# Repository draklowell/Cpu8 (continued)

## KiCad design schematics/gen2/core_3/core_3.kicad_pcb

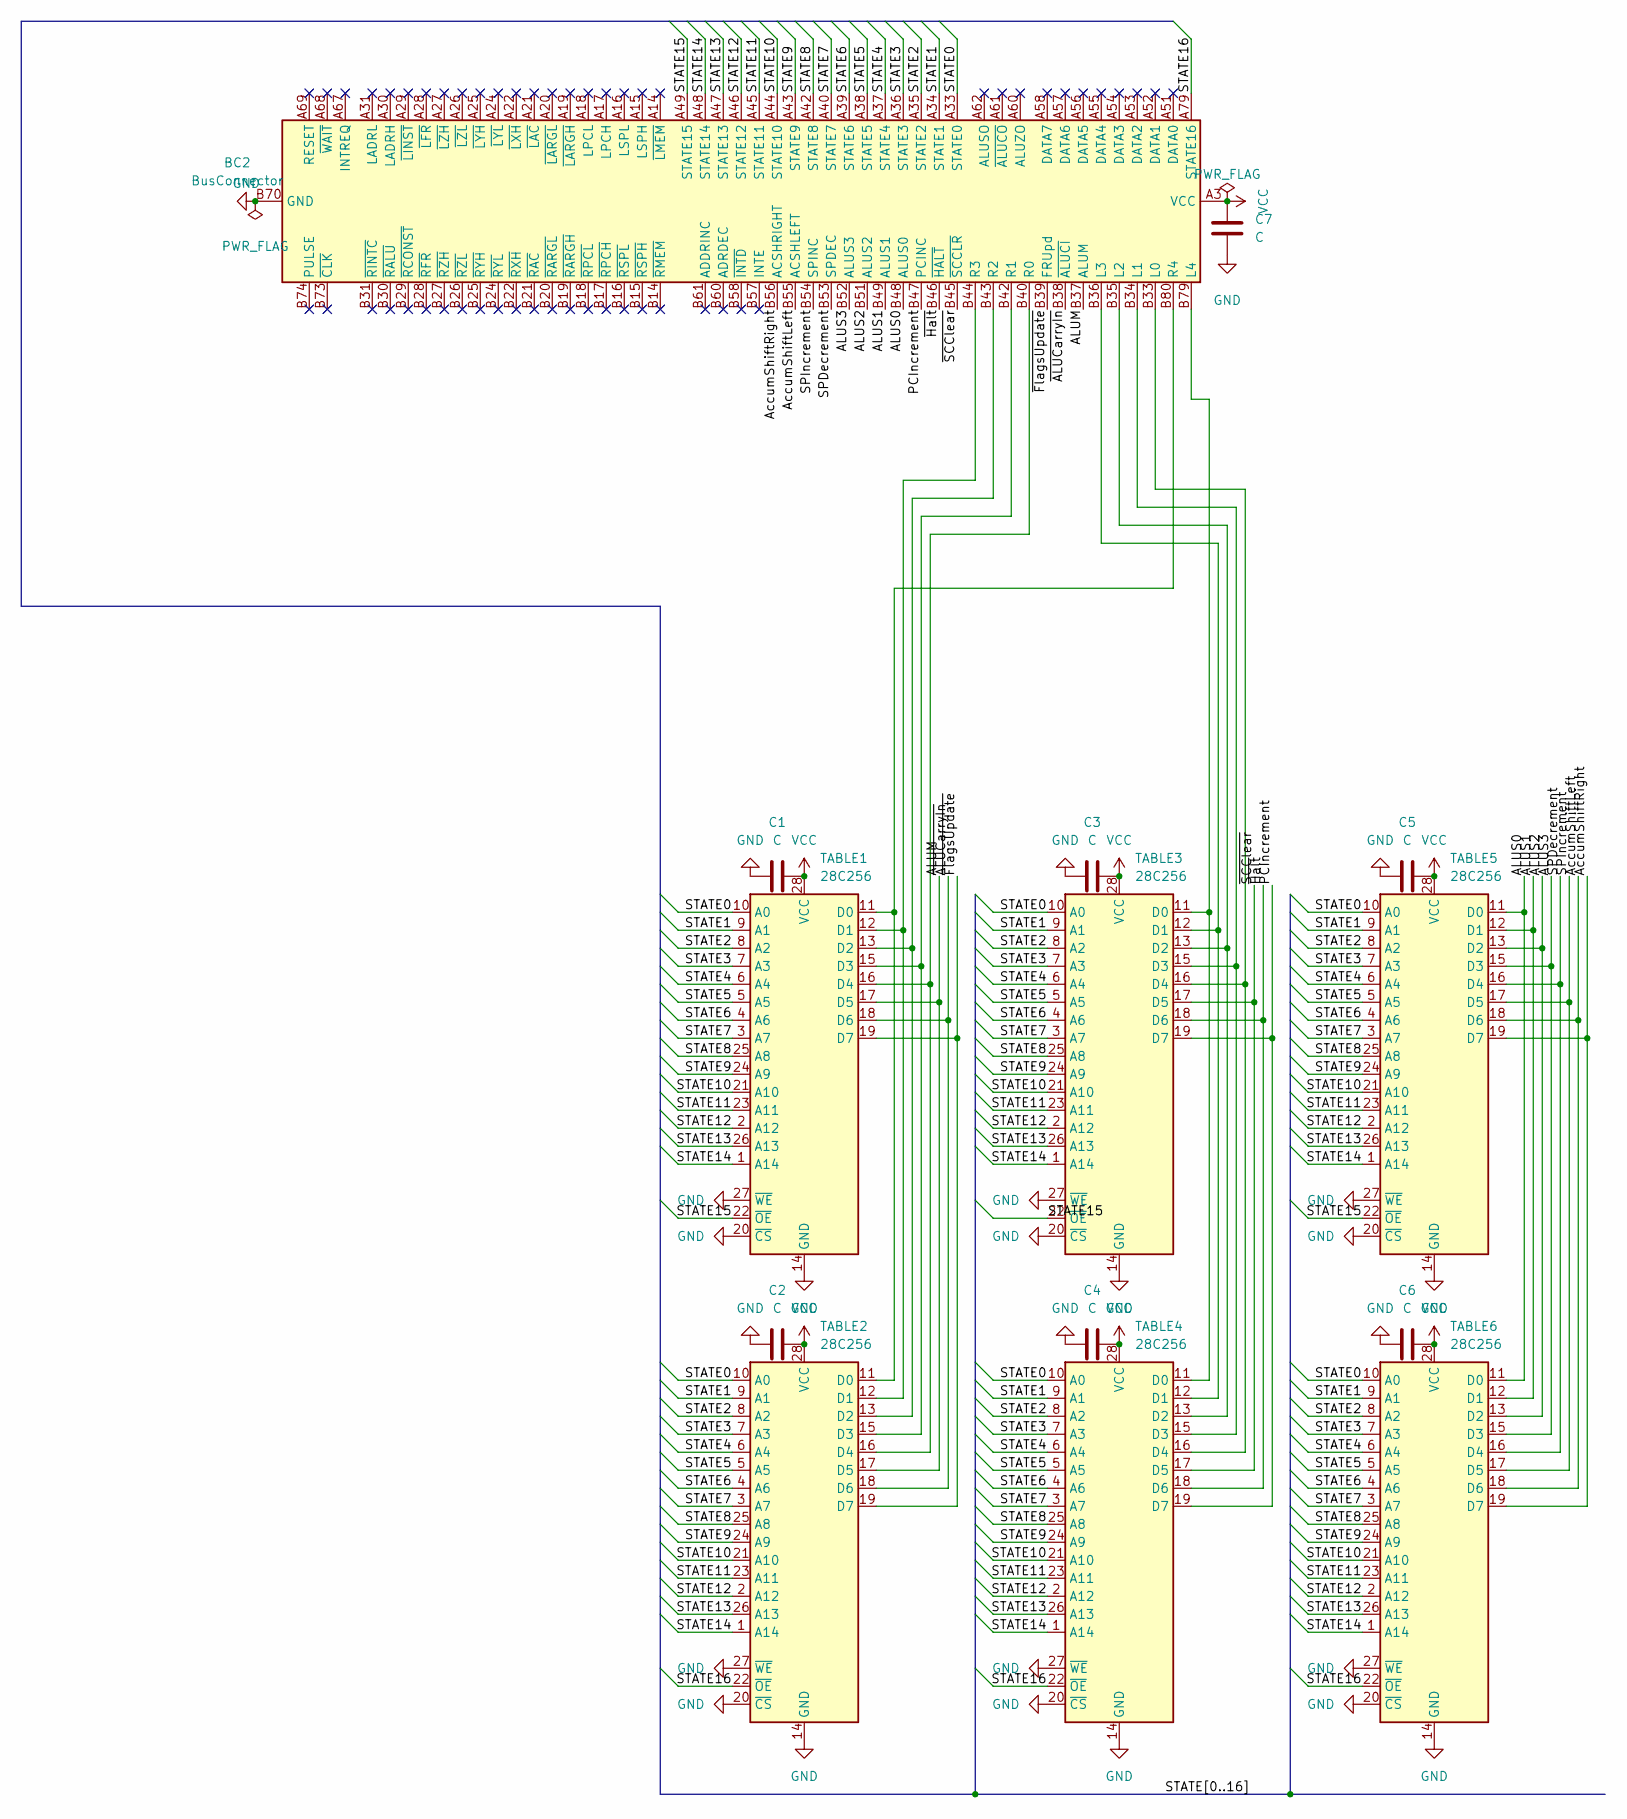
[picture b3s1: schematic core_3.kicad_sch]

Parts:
BC2: BusConnector; BUS_PCIexpress_x16
C1, C2, C3, C4, C5, C6: C; C_Disc_D5.0mm_W2.5mm_P2.50mm
C7: C; C_Radial_D6.3mm_H5.0mm_P2.50mm
TABLE1, TABLE2, TABLE3, TABLE4, TABLE5, TABLE6: 28C256; DIP-28_W15.24mm_Socket_LongPads

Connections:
/ALUM: BC2.B37 (ALUM), TABLE1.17 (D5), TABLE2.17 (D5)
/ALUS0: BC2.B48 (ALUS0), TABLE5.11 (D0), TABLE6.11 (D0)
/ALUS1: BC2.B49 (ALUS1), TABLE5.12 (D1), TABLE6.12 (D1)
/ALUS2: BC2.B51 (ALUS2), TABLE5.13 (D2), TABLE6.13 (D2)
/ALUS3: BC2.B52 (ALUS3), TABLE5.15 (D3), TABLE6.15 (D3)
/AccumShiftLeft: BC2.B55 (ACSHLEFT), TABLE5.18 (D6), TABLE6.18 (D6)
/AccumShiftRight: BC2.B56 (ACSHRIGHT), TABLE5.19 (D7), TABLE6.19 (D7)
/PCIncrement: BC2.B47 (PCINC), TABLE3.19 (D7), TABLE4.19 (D7)
/SPDecrement: BC2.B53 (SPDEC), TABLE5.16 (D4), TABLE6.16 (D4)
/SPIncrement: BC2.B54 (SPINC), TABLE5.17 (D5), TABLE6.17 (D5)
/STATE0: BC2.A33 (STATE0), TABLE1.10 (A0), TABLE2.10 (A0), TABLE3.10 (A0), TABLE4.10 (A0), TABLE5.10 (A0), TABLE6.10 (A0)
/STATE1: BC2.A34 (STATE1), TABLE1.9 (A1), TABLE2.9 (A1), TABLE3.9 (A1), TABLE4.9 (A1), TABLE5.9 (A1), TABLE6.9 (A1)
/STATE2: BC2.A35 (STATE2), TABLE1.8 (A2), TABLE2.8 (A2), TABLE3.8 (A2), TABLE4.8 (A2), TABLE5.8 (A2), TABLE6.8 (A2)
/STATE3: BC2.A36 (STATE3), TABLE1.7 (A3), TABLE2.7 (A3), TABLE3.7 (A3), TABLE4.7 (A3), TABLE5.7 (A3), TABLE6.7 (A3)
/STATE4: BC2.A37 (STATE4), TABLE1.6 (A4), TABLE2.6 (A4), TABLE3.6 (A4), TABLE4.6 (A4), TABLE5.6 (A4), TABLE6.6 (A4)
/STATE5: BC2.A38 (STATE5), TABLE1.5 (A5), TABLE2.5 (A5), TABLE3.5 (A5), TABLE4.5 (A5), TABLE5.5 (A5), TABLE6.5 (A5)
/STATE6: BC2.A39 (STATE6), TABLE1.4 (A6), TABLE2.4 (A6), TABLE3.4 (A6), TABLE4.4 (A6), TABLE5.4 (A6), TABLE6.4 (A6)
/STATE7: BC2.A40 (STATE7), TABLE1.3 (A7), TABLE2.3 (A7), TABLE3.3 (A7), TABLE4.3 (A7), TABLE5.3 (A7), TABLE6.3 (A7)
/STATE8: BC2.A42 (STATE8), TABLE1.25 (A8), TABLE2.25 (A8), TABLE3.25 (A8), TABLE4.25 (A8), TABLE5.25 (A8), TABLE6.25 (A8)
/STATE9: BC2.A43 (STATE9), TABLE1.24 (A9), TABLE2.24 (A9), TABLE3.24 (A9), TABLE4.24 (A9), TABLE5.24 (A9), TABLE6.24 (A9)
/STATE10: BC2.A44 (STATE10), TABLE1.21 (A10), TABLE2.21 (A10), TABLE3.21 (A10), TABLE4.21 (A10), TABLE5.21 (A10), TABLE6.21 (A10)
/STATE11: BC2.A45 (STATE11), TABLE1.23 (A11), TABLE2.23 (A11), TABLE3.23 (A11), TABLE4.23 (A11), TABLE5.23 (A11), TABLE6.23 (A11)
/STATE12: BC2.A46 (STATE12), TABLE1.2 (A12), TABLE2.2 (A12), TABLE3.2 (A12), TABLE4.2 (A12), TABLE5.2 (A12), TABLE6.2 (A12)
/STATE13: BC2.A47 (STATE13), TABLE1.26 (A13), TABLE2.26 (A13), TABLE3.26 (A13), TABLE4.26 (A13), TABLE5.26 (A13), TABLE6.26 (A13)
/STATE14: BC2.A48 (STATE14), TABLE1.1 (A14), TABLE2.1 (A14), TABLE3.1 (A14), TABLE4.1 (A14), TABLE5.1 (A14), TABLE6.1 (A14)
/STATE15: BC2.A49 (STATE15), TABLE1.22 (~OE), TABLE3.22 (~OE), TABLE5.22 (~OE)
/STATE16: BC2.A79 (STATE16), TABLE2.22 (~OE), TABLE4.22 (~OE), TABLE6.22 (~OE)
/~ALUCarryIn: BC2.B38 (~ALUCI), TABLE1.18 (D6), TABLE2.18 (D6)
/~FlagsUpdate: BC2.B39 (FRUpd), TABLE1.19 (D7), TABLE2.19 (D7)
/~Halt: BC2.B46 (~HALT), TABLE3.18 (D6), TABLE4.18 (D6)
/~SCClear: BC2.B45 (~SCCLR), TABLE3.17 (D5), TABLE4.17 (D5)
GND: BC2.A12 (GND), BC2.A13 (GND), BC2.A23 (GND), BC2.A32 (GND), BC2.A41 (GND), BC2.A50 (GND), BC2.A59 (GND), BC2.A63 (GND), BC2.A64 (GND), BC2.A65 (GND), BC2.A66 (GND), BC2.A70 (GND), BC2.A71 (GND), BC2.A72 (GND), BC2.A73 (GND), BC2.A74 (GND), BC2.A75 (GND), BC2.A76 (GND), BC2.B12 (GND), BC2.B13 (GND), BC2.B23 (GND), BC2.B32 (GND), BC2.B41 (GND), BC2.B50 (GND), BC2.B59 (GND), BC2.B62 (GND), BC2.B63 (GND), BC2.B64 (GND), BC2.B65 (GND), BC2.B66 (GND), BC2.B67 (GND), BC2.B68 (GND), BC2.B69 (GND), BC2.B70 (GND), BC2.B71 (GND), BC2.B72 (GND), BC2.B75 (GND), BC2.B76 (GND), C1.2, C2.2, C3.2, C4.2, C5.2, C6.2, C7.2, TABLE1.14 (GND), TABLE1.20 (~CS), TABLE1.27 (~WE), TABLE2.14 (GND), TABLE2.20 (~CS), TABLE2.27 (~WE), TABLE3.14 (GND), TABLE3.20 (~CS), TABLE3.27 (~WE), TABLE4.14 (GND), TABLE4.20 (~CS), TABLE4.27 (~WE), TABLE5.14 (GND), TABLE5.20 (~CS), TABLE5.27 (~WE), TABLE6.14 (GND), TABLE6.20 (~CS), TABLE6.27 (~WE)
unnamed: BC2.B33 (L0), TABLE3.16 (D4), TABLE4.16 (D4)
unnamed: BC2.B34 (L1), TABLE3.15 (D3), TABLE4.15 (D3)
unnamed: BC2.B35 (L2), TABLE3.13 (D2), TABLE4.13 (D2)
unnamed: BC2.B36 (L3), TABLE3.12 (D1), TABLE4.12 (D1)
unnamed: BC2.B79 (L4), TABLE3.11 (D0), TABLE4.11 (D0)
unnamed: BC2.B40 (R0), TABLE1.16 (D4), TABLE2.16 (D4)
unnamed: BC2.B42 (R1), TABLE1.15 (D3), TABLE2.15 (D3)
unnamed: BC2.B43 (R2), TABLE1.13 (D2), TABLE2.13 (D2)
unnamed: BC2.B44 (R3), TABLE1.12 (D1), TABLE2.12 (D1)
unnamed: BC2.B80 (R4), TABLE1.11 (D0), TABLE2.11 (D0)
VCC: BC2.A1 (VCC), BC2.A2 (VCC), BC2.A3 (VCC), BC2.A4 (VCC), BC2.A5 (VCC), BC2.B1 (VCC), BC2.B2 (VCC), BC2.B3 (VCC), BC2.B4 (VCC), BC2.B5 (VCC), C1.1, C2.1, C3.1, C4.1, C5.1, C6.1, C7.1, TABLE1.28 (VCC), TABLE2.28 (VCC), TABLE3.28 (VCC), TABLE4.28 (VCC), TABLE5.28 (VCC), TABLE6.28 (VCC)

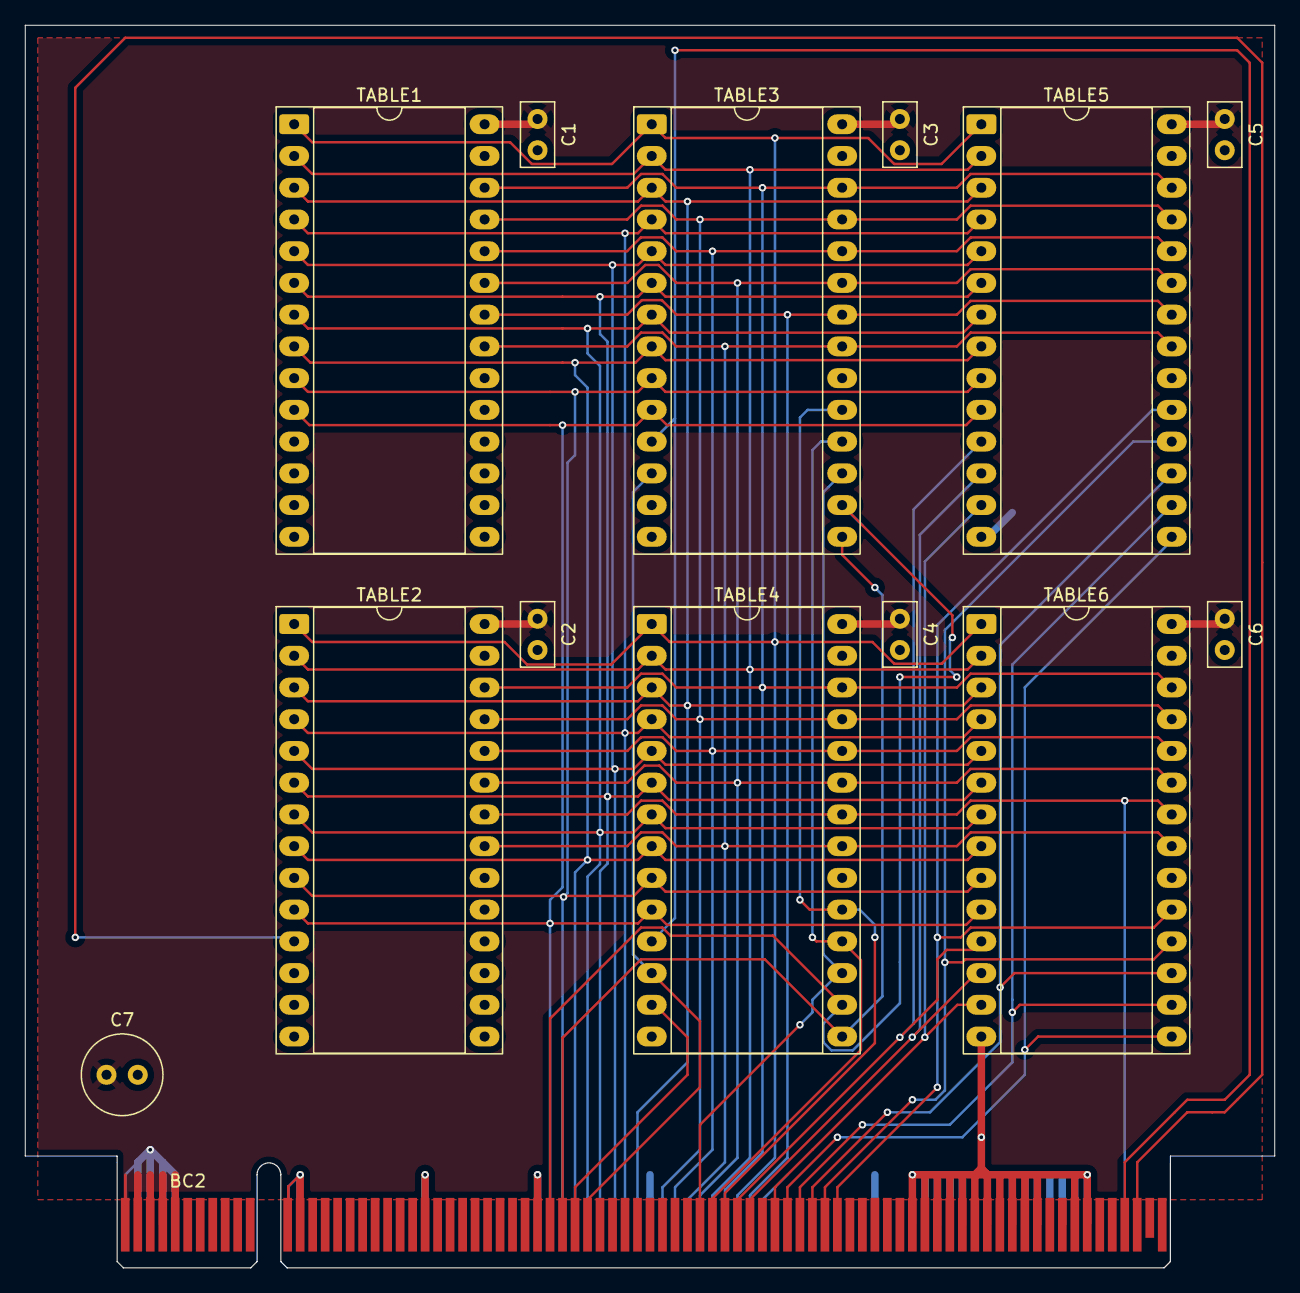
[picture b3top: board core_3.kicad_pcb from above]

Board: 2 copper layers, 100.0 x 99.4 mm, 14 parts (0 on the bottom side), 43 nets.

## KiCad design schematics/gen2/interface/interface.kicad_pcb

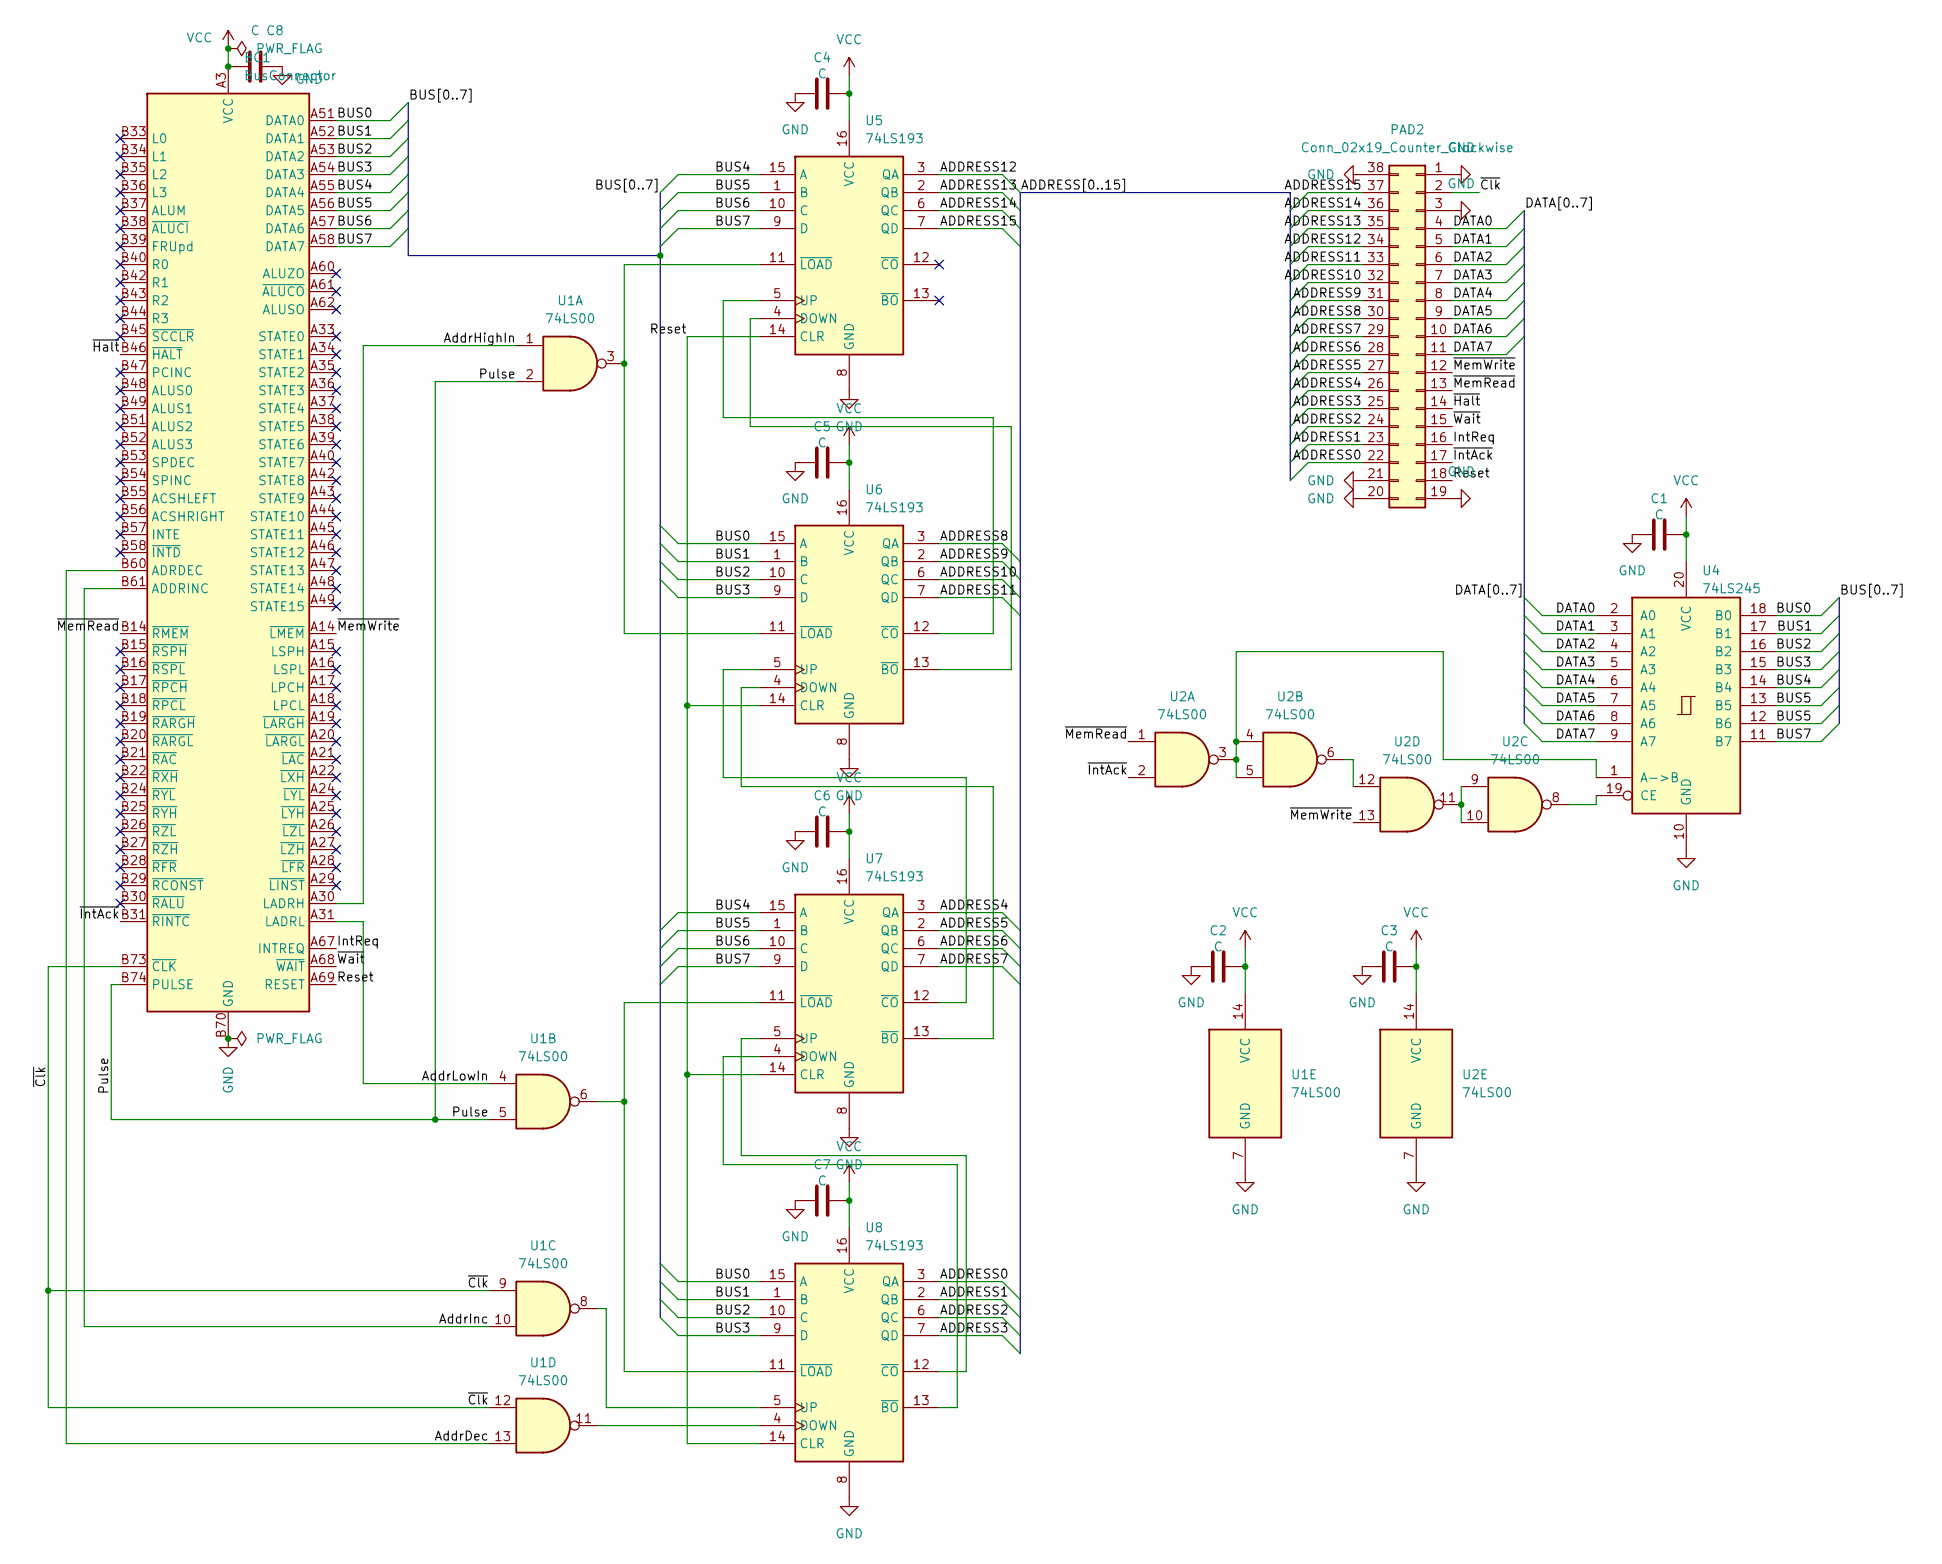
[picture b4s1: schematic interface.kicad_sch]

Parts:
BC1: BusConnector; BUS_PCIexpress_x16
C1, C2, C3, C4, C5, C6, C7: C; C_Disc_D5.0mm_W2.5mm_P5.00mm
C8: C; C_Radial_D6.3mm_H5.0mm_P2.50mm
PAD2: Conn_02x19_Counter_Clockwise; PinSocket_2x19_P2.54mm_Vertical
U1, U2: 74LS00; DIP-14_W7.62mm_Socket_LongPads
U4: 74LS245; DIP-20_W7.62mm_Socket_LongPads
U5, U6, U7, U8: 74LS193; DIP-16_W7.62mm_Socket_LongPads

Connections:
/ADDRESS0: PAD2.22, U8.3 (QA)
/ADDRESS1: PAD2.23, U8.2 (QB)
/ADDRESS2: PAD2.24, U8.6 (QC)
/ADDRESS3: PAD2.25, U8.7 (QD)
/ADDRESS4: PAD2.26, U7.3 (QA)
/ADDRESS5: PAD2.27, U7.2 (QB)
/ADDRESS6: PAD2.28, U7.6 (QC)
/ADDRESS7: PAD2.29, U7.7 (QD)
/ADDRESS8: PAD2.30, U6.3 (QA)
/ADDRESS9: PAD2.31, U6.2 (QB)
/ADDRESS10: PAD2.32, U6.6 (QC)
/ADDRESS11: PAD2.33, U6.7 (QD)
/ADDRESS12: PAD2.34, U5.3 (QA)
/ADDRESS13: PAD2.35, U5.2 (QB)
/ADDRESS14: PAD2.36, U5.6 (QC)
/ADDRESS15: PAD2.37, U5.7 (QD)
/AddrDec: BC1.B60 (ADRDEC), U1.13
/AddrHighIn: BC1.A30 (LADRH), U1.1
/AddrInc: BC1.B61 (ADDRINC), U1.10
/AddrLowIn: BC1.A31 (LADRL), U1.4
/BUS0: BC1.A51 (DATA0), U4.18 (B0), U6.15 (A), U8.15 (A)
/BUS1: BC1.A52 (DATA1), U4.17 (B1), U6.1 (B), U8.1 (B)
/BUS2: BC1.A53 (DATA2), U4.16 (B2), U6.10 (C), U8.10 (C)
/BUS3: BC1.A54 (DATA3), U4.15 (B3), U6.9 (D), U8.9 (D)
/BUS4: BC1.A55 (DATA4), U4.14 (B4), U5.15 (A), U7.15 (A)
/BUS5: BC1.A56 (DATA5), U4.12 (B6), U4.13 (B5), U5.1 (B), U7.1 (B)
/BUS6: BC1.A57 (DATA6), U5.10 (C), U7.10 (C)
/BUS7: BC1.A58 (DATA7), U4.11 (B7), U5.9 (D), U7.9 (D)
/DATA0: PAD2.4, U4.2 (A0)
/DATA1: PAD2.5, U4.3 (A1)
/DATA2: PAD2.6, U4.4 (A2)
/DATA3: PAD2.7, U4.5 (A3)
/DATA4: PAD2.8, U4.6 (A4)
/DATA5: PAD2.9, U4.7 (A5)
/DATA6: PAD2.10, U4.8 (A6)
/DATA7: PAD2.11, U4.9 (A7)
/IntReq: BC1.A67 (INTREQ), PAD2.16
/Pulse: BC1.B74 (PULSE), U1.2, U1.5
/Reset: BC1.A69 (RESET), PAD2.18, U5.14 (CLR), U6.14 (CLR), U7.14 (CLR), U8.14 (CLR)
/~Clk: BC1.B73 (~CLK), PAD2.2, U1.9, U1.12
/~Halt: BC1.B46 (~HALT), PAD2.14
/~IntAck: BC1.B31 (~RINTC), PAD2.17, U2.2
/~MemRead: BC1.B14 (~RMEM), PAD2.13, U2.1
/~MemWrite: BC1.A14 (~LMEM), PAD2.12, U2.13
/~Wait: BC1.A68 (~WAIT), PAD2.15
GND: BC1.A12 (GND), BC1.A13 (GND), BC1.A23 (GND), BC1.A32 (GND), BC1.A41 (GND), BC1.A50 (GND), BC1.A59 (GND), BC1.A63 (GND), BC1.A64 (GND), BC1.A65 (GND), BC1.A66 (GND), BC1.A70 (GND), BC1.A71 (GND), BC1.A72 (GND), BC1.A73 (GND), BC1.A74 (GND), BC1.A75 (GND), BC1.A76 (GND), BC1.B12 (GND), BC1.B13 (GND), BC1.B23 (GND), BC1.B32 (GND), BC1.B41 (GND), BC1.B50 (GND), BC1.B59 (GND), BC1.B62 (GND), BC1.B63 (GND), BC1.B64 (GND), BC1.B65 (GND), BC1.B66 (GND), BC1.B67 (GND), BC1.B68 (GND), BC1.B69 (GND), BC1.B70 (GND), BC1.B71 (GND), BC1.B72 (GND), BC1.B75 (GND), BC1.B76 (GND), C1.2, C2.2, C3.2, C4.2, C5.2, C6.2, C7.2, C8.2, PAD2.1, PAD2.3, PAD2.19, PAD2.20, PAD2.21, PAD2.38, U1.7 (GND), U2.7 (GND), U4.10 (GND), U5.8 (GND), U6.8 (GND), U7.8 (GND), U8.8 (GND)
unnamed: U2.9, U2.10, U2.11
unnamed: U2.6, U2.12
unnamed: U2.3, U2.4, U2.5, U4.1 (A->B)
unnamed: U2.8, U4.19 (CE)
unnamed: U5.4 (DOWN), U6.13 (~BO)
unnamed: U5.5 (UP), U6.12 (~CO)
unnamed: U1.3, U5.11 (~LOAD), U6.11 (~LOAD)
unnamed: U6.4 (DOWN), U7.13 (~BO)
unnamed: U6.5 (UP), U7.12 (~CO)
unnamed: U7.4 (DOWN), U8.13 (~BO)
unnamed: U7.5 (UP), U8.12 (~CO)
unnamed: U1.6, U7.11 (~LOAD), U8.11 (~LOAD)
unnamed: U1.11, U8.4 (DOWN)
unnamed: U1.8, U8.5 (UP)
VCC: BC1.A1 (VCC), BC1.A2 (VCC), BC1.A3 (VCC), BC1.A4 (VCC), BC1.A5 (VCC), BC1.B1 (VCC), BC1.B2 (VCC), BC1.B3 (VCC), BC1.B4 (VCC), BC1.B5 (VCC), C1.1, C2.1, C3.1, C4.1, C5.1, C6.1, C7.1, C8.1, U1.14 (VCC), U2.14 (VCC), U4.20 (VCC), U5.16 (VCC), U6.16 (VCC), U7.16 (VCC), U8.16 (VCC)

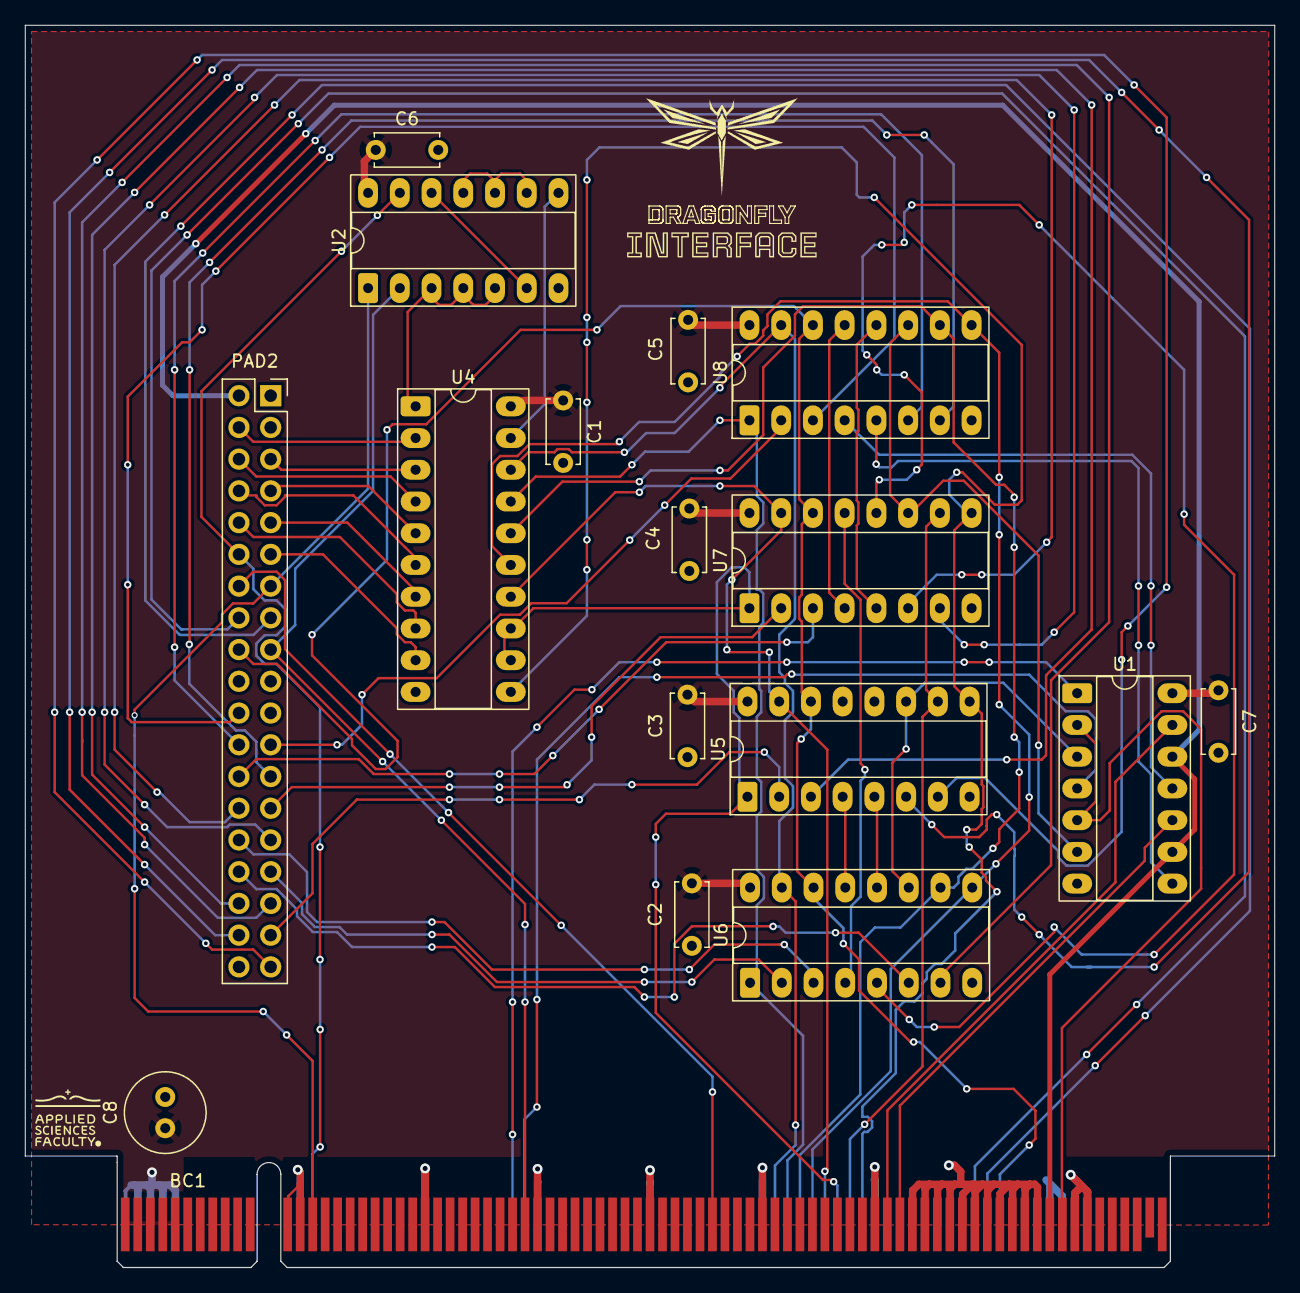
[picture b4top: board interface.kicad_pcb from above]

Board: 2 copper layers, 100.0 x 99.4 mm, 18 parts (0 on the bottom side), 61 nets.

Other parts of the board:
kibuzzard-6911D1BC: G***; kibuzzard-6911D1BC

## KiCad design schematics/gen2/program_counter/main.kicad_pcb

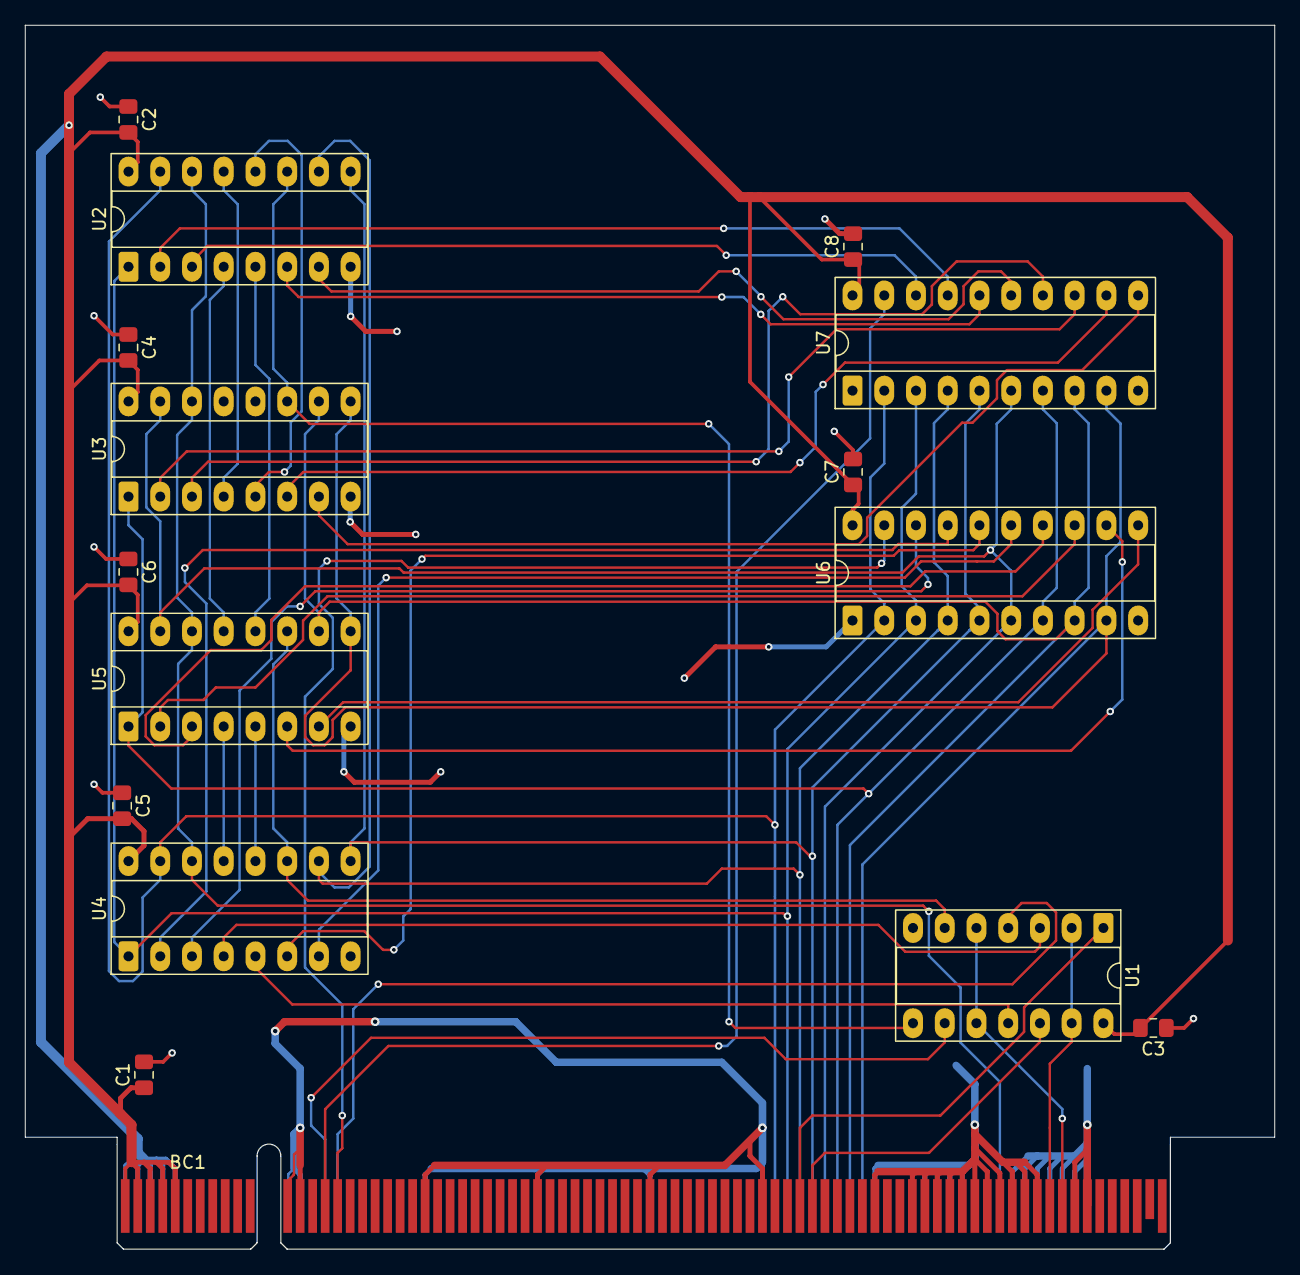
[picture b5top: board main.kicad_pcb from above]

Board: 2 copper layers, 100.0 x 97.9 mm, 16 parts (0 on the bottom side), 45 nets.

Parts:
BC1: BusConnector; BUS_PCIexpress_x16
C1, C2, C3, C4, C5, C6, C7, C8: C; C_0805_2012Metric_Pad1.18x1.45mm_HandSolder
U1: 74HC00; DIP-14_W7.62mm_Socket_LongPads
U2, U3, U4, U5: 74HC193; DIP-16_W7.62mm_Socket_LongPads
U6, U7: 74HC245; DIP-20_W7.62mm_Socket_LongPads

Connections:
/CPd: U1.3, U4.4 (DOWN)
/CPu: U1.11, U4.5 (UP)
/DATA0: BC1.A51 (DATA0), U2.15 (A), U4.15 (A), U6.2 (A0), U7.2 (A0)
/DATA1: BC1.A52 (DATA1), U2.1 (B), U4.1 (B), U6.3 (A1), U7.3 (A1)
/DATA2: BC1.A53 (DATA2), U2.10 (C), U4.10 (C), U6.4 (A2), U7.4 (A2)
/DATA3: BC1.A54 (DATA3), U2.9 (D), U4.9 (D), U6.5 (A3), U7.5 (A3)
/DATA4: BC1.A55 (DATA4), U3.15 (A), U5.15 (A), U6.6 (A4), U7.6 (A4)
/DATA5: BC1.A56 (DATA5), U3.1 (B), U5.1 (B), U6.7 (A5), U7.7 (A5)
/DATA6: BC1.A57 (DATA6), U3.10 (C), U5.10 (C), U6.8 (A6), U7.8 (A6)
/DATA7: BC1.A58 (DATA7), U3.9 (D), U5.9 (D), U6.9 (A7), U7.9 (A7)
/DH0: U2.3 (QA), U7.18 (B0)
/DH1: U2.2 (QB), U7.17 (B1)
/DH2: U2.6 (QC), U7.16 (B2)
/DH3: U2.7 (QD), U7.15 (B3)
/DH4: U3.3 (QA), U7.14 (B4)
/DH5: U3.2 (QB), U7.13 (B5)
/DH6: U3.6 (QC), U7.12 (B6)
/DH7: U3.7 (QD), U7.11 (B7)
/DL0: U4.3 (QA), U6.18 (B0)
/DL1: U4.2 (QB), U6.17 (B1)
/DL2: U4.6 (QC), U6.16 (B2)
/DL3: U4.7 (QD), U6.15 (B3)
/DL4: U5.3 (QA), U6.14 (B4)
/DL5: U5.2 (QB), U6.13 (B5)
/DL6: U5.6 (QC), U6.12 (B6)
/DL7: U5.7 (QD), U6.11 (B7)
/LSPH: BC1.A15 (LSPH), U1.9
/LSPL: BC1.A16 (LSPL), U1.4
/PULSE: BC1.B74 (PULSE), U1.5, U1.10
/Ph: U1.8, U2.11 (~LOAD), U3.11 (~LOAD)
/Pl: U1.6, U4.11 (~LOAD), U5.11 (~LOAD)
/RESET: BC1.A69 (RESET), U2.14 (CLR), U3.14 (CLR), U4.14 (CLR), U5.14 (CLR)
/SPDEC: BC1.B53 (SPDEC), U1.1
/SPINC: BC1.B54 (SPINC), U1.12
/~CLK: BC1.B73 (~CLK), U1.2, U1.13
/~RSPH: BC1.B15 (~RSPH), U7.19 (CE)
/~RSPL: BC1.B16 (~RSPL), U6.19 (CE)
GND: BC1.A12 (GND), BC1.A13 (GND), BC1.A23 (GND), BC1.A32 (GND), BC1.A41 (GND), BC1.A50 (GND), BC1.A59 (GND), BC1.A63 (GND), BC1.A64 (GND), BC1.A65 (GND), BC1.A66 (GND), BC1.A70 (GND), BC1.A71 (GND), BC1.A72 (GND), BC1.A73 (GND), BC1.A74 (GND), BC1.A75 (GND), BC1.A76 (GND), BC1.B12 (GND), BC1.B13 (GND), BC1.B23 (GND), BC1.B32 (GND), BC1.B41 (GND), BC1.B50 (GND), BC1.B59 (GND), BC1.B62 (GND), BC1.B63 (GND), BC1.B64 (GND), BC1.B65 (GND), BC1.B66 (GND), BC1.B67 (GND), BC1.B68 (GND), BC1.B69 (GND), BC1.B70 (GND), BC1.B71 (GND), BC1.B72 (GND), BC1.B75 (GND), BC1.B76 (GND), C1.2, C2.1, C3.1, C4.1, C5.1, C6.1, C7.2, C8.2, U1.7 (GND), U2.8 (GND), U3.8 (GND), U4.8 (GND), U5.8 (GND), U6.1 (A->B), U6.10 (GND), U7.1 (A->B), U7.10 (GND)
unnamed: U2.4 (DOWN), U5.13 (~BO)
unnamed: U2.5 (UP), U5.12 (~CO)
unnamed: U2.13 (~BO), U3.4 (DOWN)
unnamed: U2.12 (~CO), U3.5 (UP)
unnamed: U4.13 (~BO), U5.4 (DOWN)
unnamed: U4.12 (~CO), U5.5 (UP)
VCC: BC1.A1 (VCC), BC1.A2 (VCC), BC1.A3 (VCC), BC1.A4 (VCC), BC1.A5 (VCC), BC1.B1 (VCC), BC1.B2 (VCC), BC1.B3 (VCC), BC1.B4 (VCC), BC1.B5 (VCC), C1.1, C2.2, C3.2, C4.2, C5.2, C6.2, C7.1, C8.1, U1.14 (VCC), U2.16 (VCC), U3.16 (VCC), U4.16 (VCC), U5.16 (VCC), U6.20 (VCC), U7.20 (VCC)

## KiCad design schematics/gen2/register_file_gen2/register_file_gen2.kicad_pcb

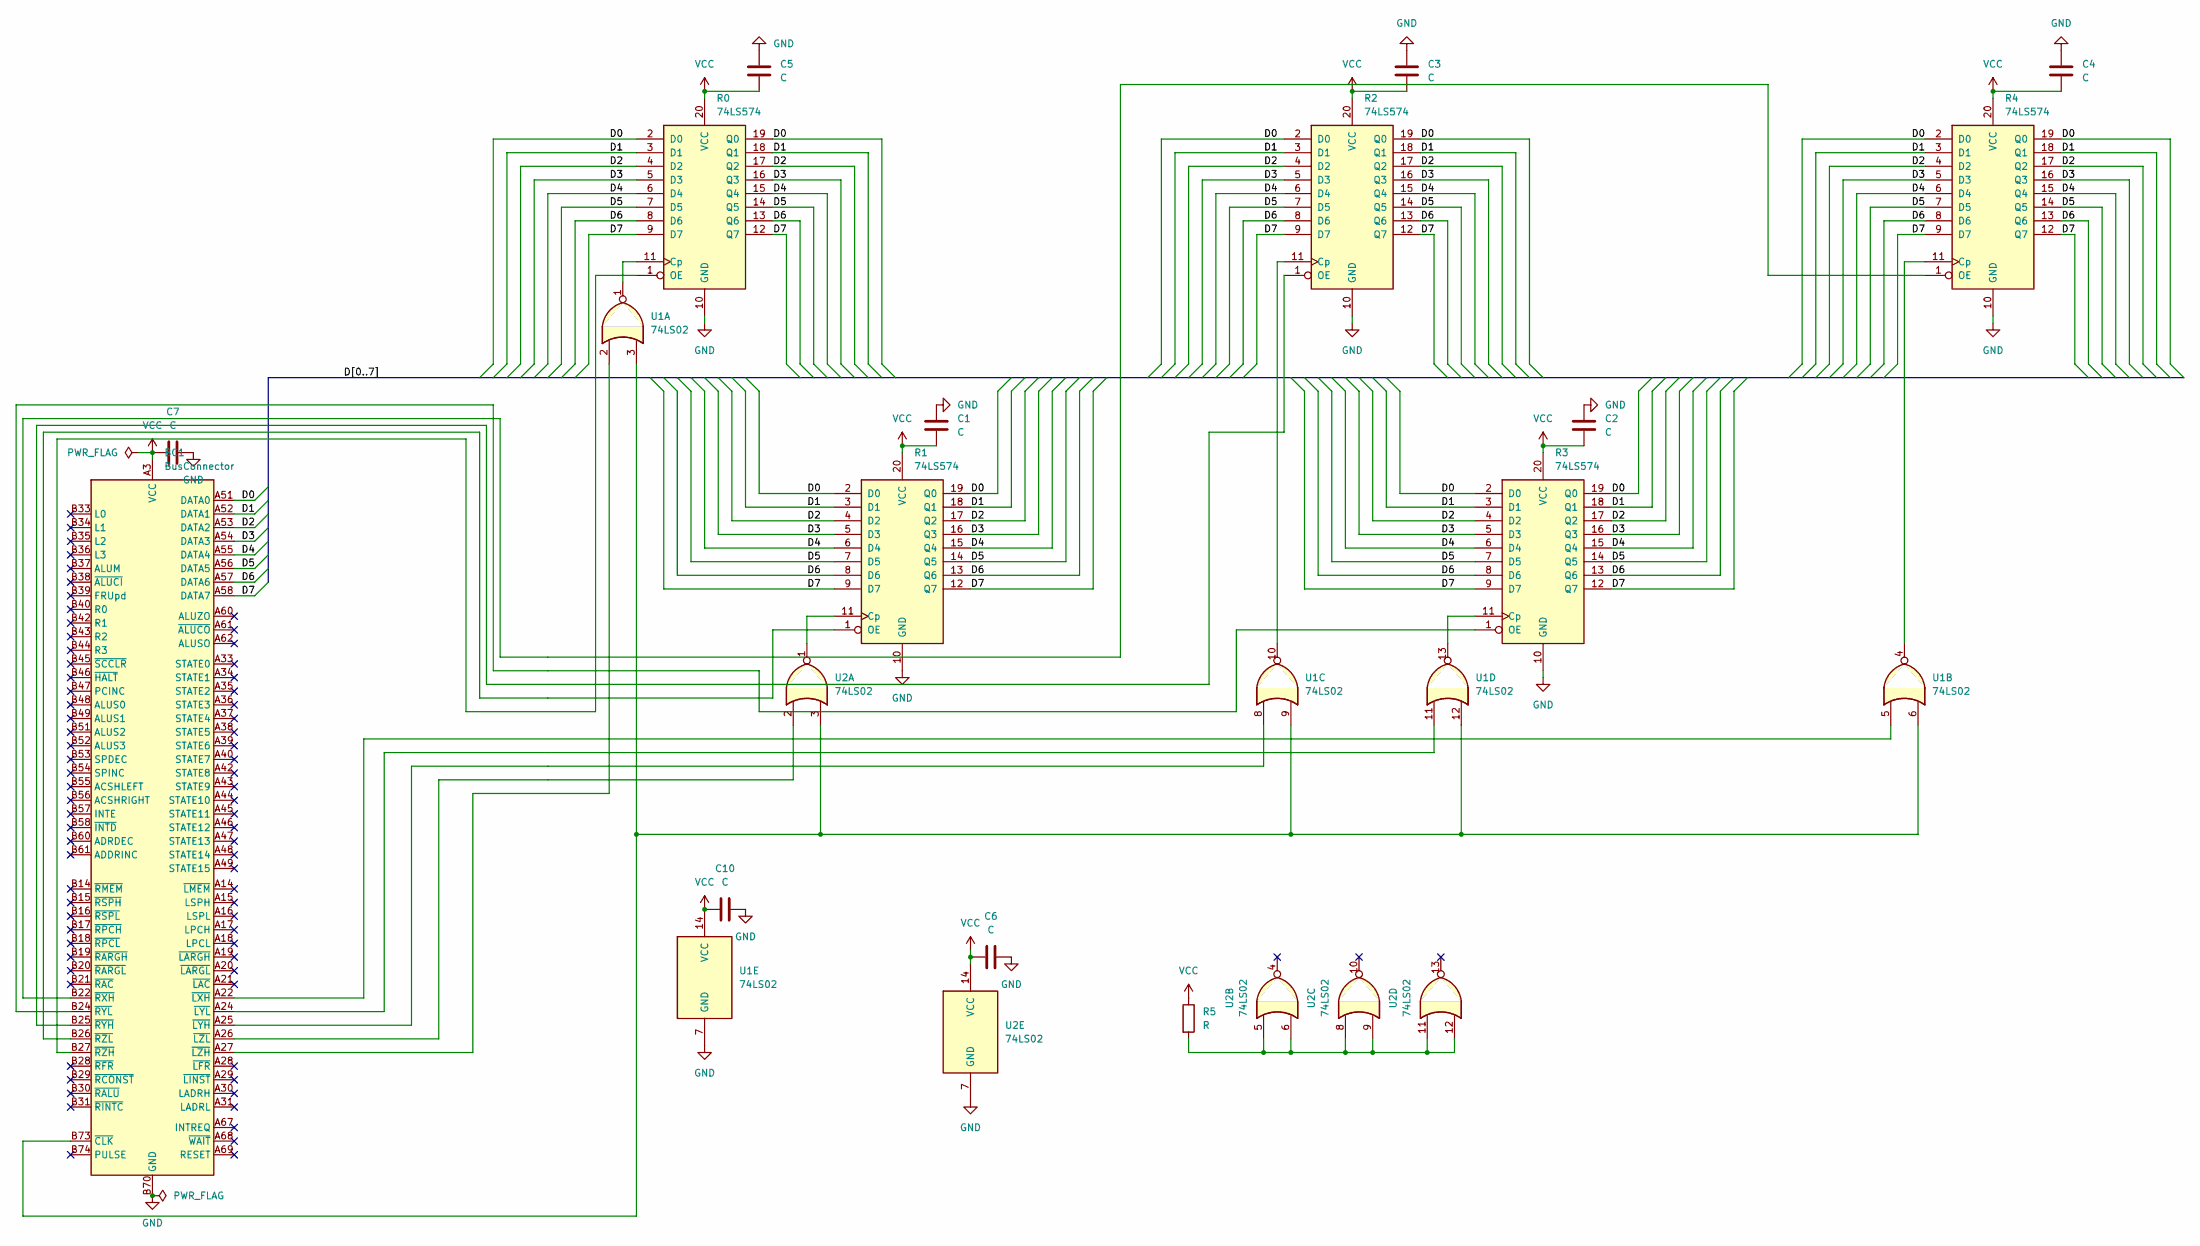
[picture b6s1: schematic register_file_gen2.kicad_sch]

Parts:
BC1: BusConnector; BUS_PCIexpress_x16
C1, C2, C3, C4, C5, C6, C10: C; C_Disc_D5.0mm_W2.5mm_P5.00mm
C7: C; C_Radial_D6.3mm_H5.0mm_P2.50mm
R0, R1, R2, R3, R4: 74LS574; DIP-20_W7.62mm_Socket_LongPads
R5: R; R_Axial_DIN0207_L6.3mm_D2.5mm_P7.62mm_Horizontal
U1, U2: 74LS02; DIP-14_W7.62mm_Socket_LongPads

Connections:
/D0: BC1.A51 (DATA0), R0.2 (D0), R0.19 (Q0), R1.2 (D0), R1.19 (Q0), R2.2 (D0), R2.19 (Q0), R3.2 (D0), R3.19 (Q0), R4.2 (D0), R4.19 (Q0)
/D1: BC1.A52 (DATA1), R0.3 (D1), R0.18 (Q1), R1.3 (D1), R1.18 (Q1), R2.3 (D1), R2.18 (Q1), R3.3 (D1), R3.18 (Q1), R4.3 (D1), R4.18 (Q1)
/D2: BC1.A53 (DATA2), R0.4 (D2), R0.17 (Q2), R1.4 (D2), R1.17 (Q2), R2.4 (D2), R2.17 (Q2), R3.4 (D2), R3.17 (Q2), R4.4 (D2), R4.17 (Q2)
/D3: BC1.A54 (DATA3), R0.5 (D3), R0.16 (Q3), R1.5 (D3), R1.16 (Q3), R2.5 (D3), R2.16 (Q3), R3.5 (D3), R3.16 (Q3), R4.5 (D3), R4.16 (Q3)
/D4: BC1.A55 (DATA4), R0.6 (D4), R0.15 (Q4), R1.6 (D4), R1.15 (Q4), R2.6 (D4), R2.15 (Q4), R3.6 (D4), R3.15 (Q4), R4.6 (D4), R4.15 (Q4)
/D5: BC1.A56 (DATA5), R0.7 (D5), R0.14 (Q5), R1.7 (D5), R1.14 (Q5), R2.7 (D5), R2.14 (Q5), R3.7 (D5), R3.14 (Q5), R4.7 (D5), R4.14 (Q5)
/D6: BC1.A57 (DATA6), R0.8 (D6), R0.13 (Q6), R1.8 (D6), R1.13 (Q6), R2.8 (D6), R2.13 (Q6), R3.8 (D6), R3.13 (Q6), R4.8 (D6), R4.13 (Q6)
/D7: BC1.A58 (DATA7), R0.9 (D7), R0.12 (Q7), R1.9 (D7), R1.12 (Q7), R2.9 (D7), R2.12 (Q7), R3.9 (D7), R3.12 (Q7), R4.9 (D7), R4.12 (Q7)
GND: BC1.A12 (GND), BC1.A13 (GND), BC1.A23 (GND), BC1.A32 (GND), BC1.A41 (GND), BC1.A50 (GND), BC1.A59 (GND), BC1.A63 (GND), BC1.A64 (GND), BC1.A65 (GND), BC1.A66 (GND), BC1.A70 (GND), BC1.A71 (GND), BC1.A72 (GND), BC1.A73 (GND), BC1.A74 (GND), BC1.A75 (GND), BC1.A76 (GND), BC1.B12 (GND), BC1.B13 (GND), BC1.B23 (GND), BC1.B32 (GND), BC1.B41 (GND), BC1.B50 (GND), BC1.B59 (GND), BC1.B62 (GND), BC1.B63 (GND), BC1.B64 (GND), BC1.B65 (GND), BC1.B66 (GND), BC1.B67 (GND), BC1.B68 (GND), BC1.B69 (GND), BC1.B70 (GND), BC1.B71 (GND), BC1.B72 (GND), BC1.B75 (GND), BC1.B76 (GND), C1.1, C2.1, C3.1, C4.1, C5.1, C6.2, C7.2, C10.2, R0.10 (GND), R1.10 (GND), R2.10 (GND), R3.10 (GND), R4.10 (GND), U1.7 (GND), U2.7 (GND)
unnamed: BC1.B73 (~CLK), U1.3, U1.6, U1.9, U1.12, U2.3
unnamed: BC1.A22 (~LXH), U1.5
unnamed: BC1.A25 (~LYH), U1.8
unnamed: BC1.A24 (~LYL), U1.11
unnamed: BC1.A27 (~LZH), U1.2
unnamed: BC1.A26 (~LZL), U2.2
unnamed: BC1.B22 (~RXH), R4.1 (OE)
unnamed: BC1.B25 (~RYH), R2.1 (OE)
unnamed: BC1.B24 (~RYL), R3.1 (OE)
unnamed: BC1.B27 (~RZH), R0.1 (OE)
unnamed: BC1.B26 (~RZL), R1.1 (OE)
unnamed: R0.11 (Cp), U1.1
unnamed: R1.11 (Cp), U2.1
unnamed: R2.11 (Cp), U1.10
unnamed: R3.11 (Cp), U1.13
unnamed: R4.11 (Cp), U1.4
unnamed: R5.2, U2.5, U2.6, U2.8, U2.9, U2.11, U2.12
VCC: BC1.A1 (VCC), BC1.A2 (VCC), BC1.A3 (VCC), BC1.A4 (VCC), BC1.A5 (VCC), BC1.B1 (VCC), BC1.B2 (VCC), BC1.B3 (VCC), BC1.B4 (VCC), BC1.B5 (VCC), C1.2, C2.2, C3.2, C4.2, C5.2, C6.1, C7.1, C10.1, R0.20 (VCC), R1.20 (VCC), R2.20 (VCC), R3.20 (VCC), R4.20 (VCC), R5.1, U1.14 (VCC), U2.14 (VCC)
